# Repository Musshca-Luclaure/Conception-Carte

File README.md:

# Conception-Carte
Branch Daughter-Board -- Stage 1A
Branch Controle_suivant_champ_magnetique  -- Projet Contrôle d'une voiture

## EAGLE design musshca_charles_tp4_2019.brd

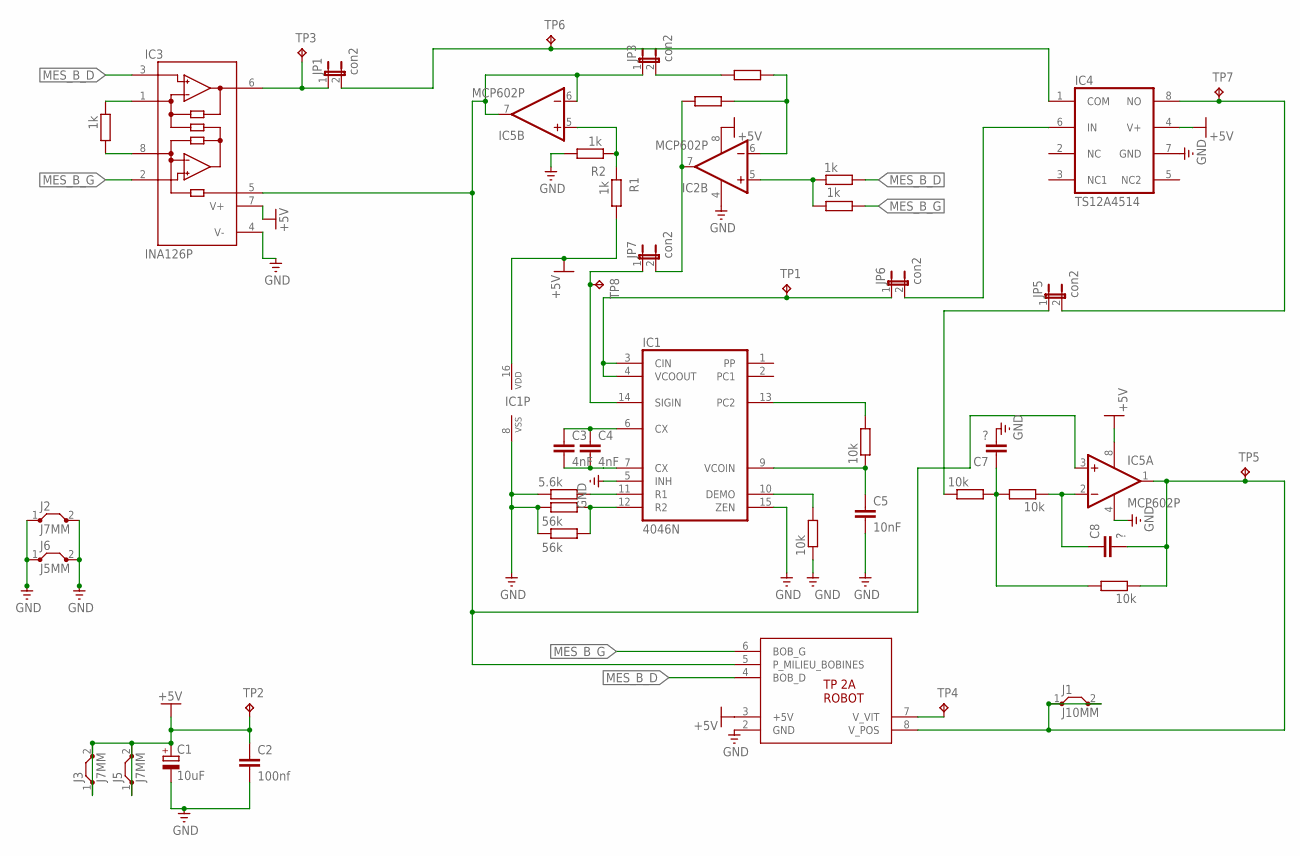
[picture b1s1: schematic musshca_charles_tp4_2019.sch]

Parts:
C1: 10uF; E2,5-7
C2: 100nf; C050-030X075
C3, C4: 4nF; C050-030X075
C5: 10nF; C050-030X075
C7, C8: ?; C050-030X075
IC1: 4046N; DIL16
IC2, IC5: MCP602P; DIL08
IC3: INA126P; DIL08
IC4: TS12A4514; DIL08
J1: J10MM; 10
J2, J3, J5: J7MM; 07
J6: J5MM; 05
JP1, JP3, JP5, JP6, JP7: con2; JP1
R1, R2, R3, R4, R6, R7: 1k; RC07
R5: 5.6k; RC07
R8, R9: 56k; RC07
R10, R11, R12, R13, R14: 10k; RC07
RG: 1k; RC07
TP1, TP2, TP3, TP4, TP5, TP6, TP7, TP8: TPPAD1-13; P1-13
U$1: TP2A_ROBOT

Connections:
+5V: C1.+, C2.1, IC1.16 (VDD), IC2.8 (V+), IC3.7 (V+), IC4.4 (V+), IC5.8 (V+), J3.1, J3.2, J5.1, J5.2, R1.P$2 (2), TP2.TP, U$1.3 (+5V)
GND: C1.-, C2.2, C5.2, C7.2, IC1.5 (INH), IC1.8 (VSS), IC1.15 (ZEN), IC2.4 (V-), IC3.4 (V-), IC4.7 (GND), IC5.4 (V-), J2.1, J2.2, J6.1, J6.2, R2.P$2 (2), R5.P$2 (2), R8.P$2 (2), R9.P$2 (2), R11.P$2 (2), U$1.2 (GND)
MES_B_D: IC3.3 (+IN), R3.P$1 (1), U$1.4 (BOB_D)
MES_B_G: IC3.2 (-IN), R4.P$2 (2), U$1.6 (BOB_G)
unnamed: JP5.1, R13.P$2 (2)
unnamed: IC3.6 (OUT), JP1.1, TP3.TP
unnamed: TP4.TP, U$1.7 (V_VIT)
unnamed: IC3.8 (RG), RG.P$2 (2)
unnamed: IC3.1 (RG), RG.P$1 (1)
unnamed: IC5.5 (+IN), R1.P$1 (1), R2.P$1 (1)
unnamed: IC3.5 (REF), IC5.3 (+IN), IC5.6 (-IN), IC5.7 (OUT), JP3.1, U$1.5 (P_MILIEU_BOBINES)
unnamed: C8.2, IC5.1 (OUT), J1.1, J1.2, R14.P$2 (2), TP5.TP, U$1.8 (V_POS)
unnamed: IC4.1 (COM), JP1.2, TP6.TP
unnamed: IC2.5 (+IN), R3.P$2 (2), R4.P$1 (1)
unnamed: IC4.8 (NO), JP5.2, TP7.TP
unnamed: IC2.7 (OUT), JP7.2, R6.P$2 (2)
unnamed: IC2.6 (-IN), R6.P$1 (1), R7.P$2 (2)
unnamed: IC1.11 (R1), R5.P$1 (1)
unnamed: C7.1, R12.P$1 (1), R13.P$1 (1), R14.P$1 (1)
unnamed: IC1.12 (R2), R8.P$1 (1), R9.P$1 (1)
unnamed: C3.1, C4.1, IC1.6 (CX)
unnamed: C3.2, C4.2, IC1.7 (CX)
unnamed: IC4.6 (IN), JP6.2
unnamed: IC1.10 (DEMO), R11.P$1 (1)
unnamed: IC1.13 (PC2), R10.P$1 (1)
unnamed: C5.1, IC1.9 (VCOIN), R10.P$2 (2)
unnamed: JP3.2, R7.P$1 (1)
unnamed: C8.1, IC5.2 (-IN), R12.P$2 (2)
unnamed: IC1.3 (CIN), IC1.4 (VCOOUT), JP6.1, TP1.TP
unnamed: IC1.14 (SIGIN), JP7.1, TP8.TP

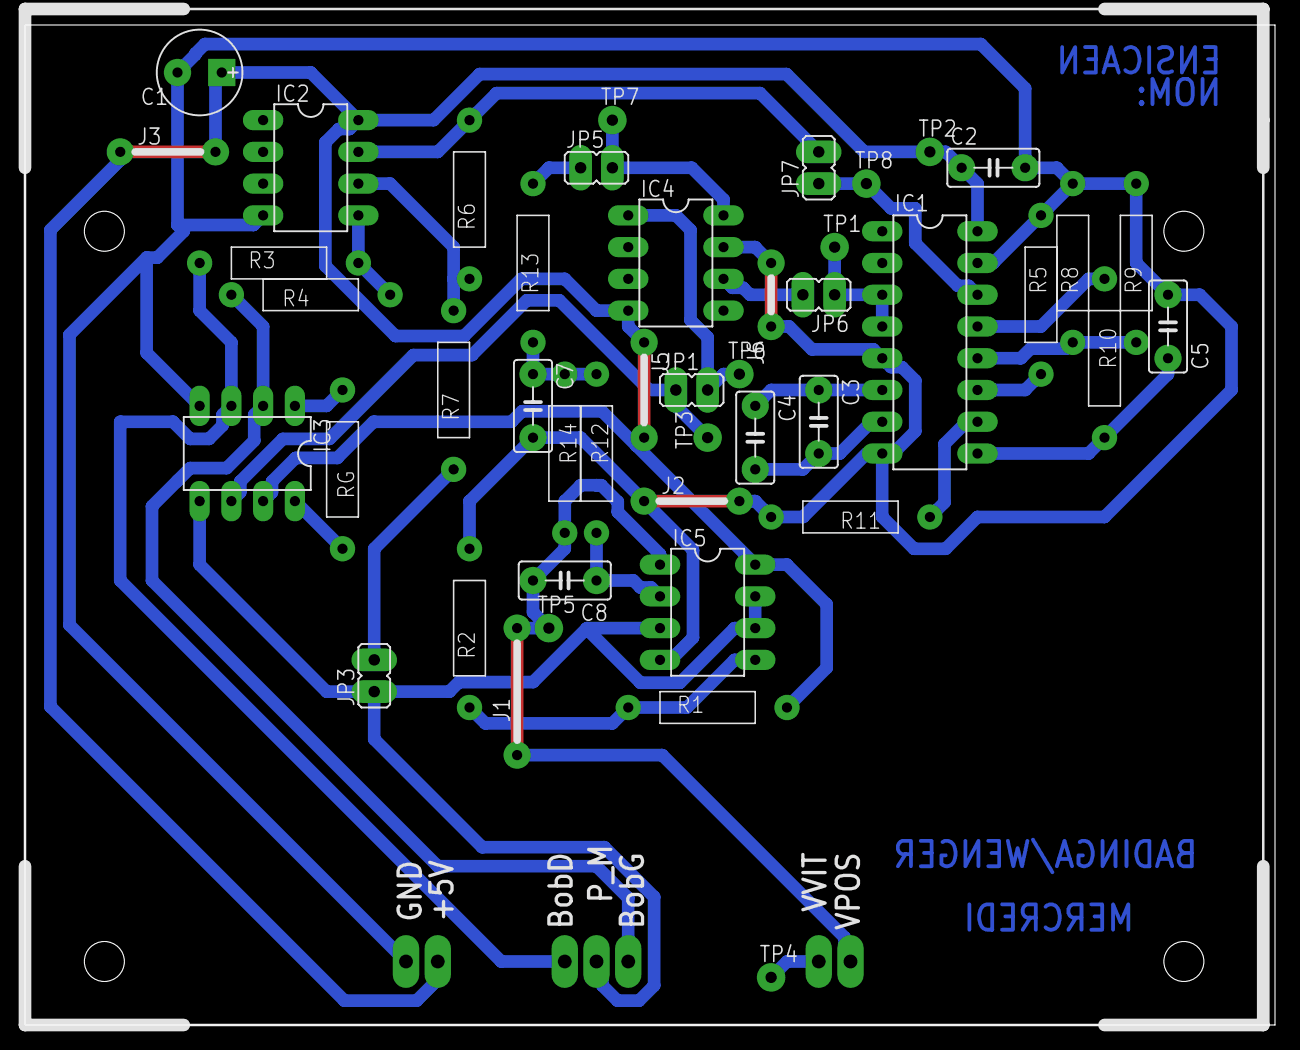
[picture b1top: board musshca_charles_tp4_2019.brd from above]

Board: 2 copper layers, 100.0 x 80.0 mm, 46 parts (0 on the bottom side), 30 nets.

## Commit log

2021-01-17 fichier gerber et pdf carte lcd
2021-01-17 fichier technique et pdf
2021-01-17 ajout photo carte
2021-01-17 pdf schematic et layouy

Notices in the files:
parts and their libraries:
supply0: Copyright (C) 2007, Bob Starr
